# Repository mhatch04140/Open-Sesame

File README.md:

README
======
# Description
Open Sesame is a project to develope a prototype voice enabled car door opening Android application.

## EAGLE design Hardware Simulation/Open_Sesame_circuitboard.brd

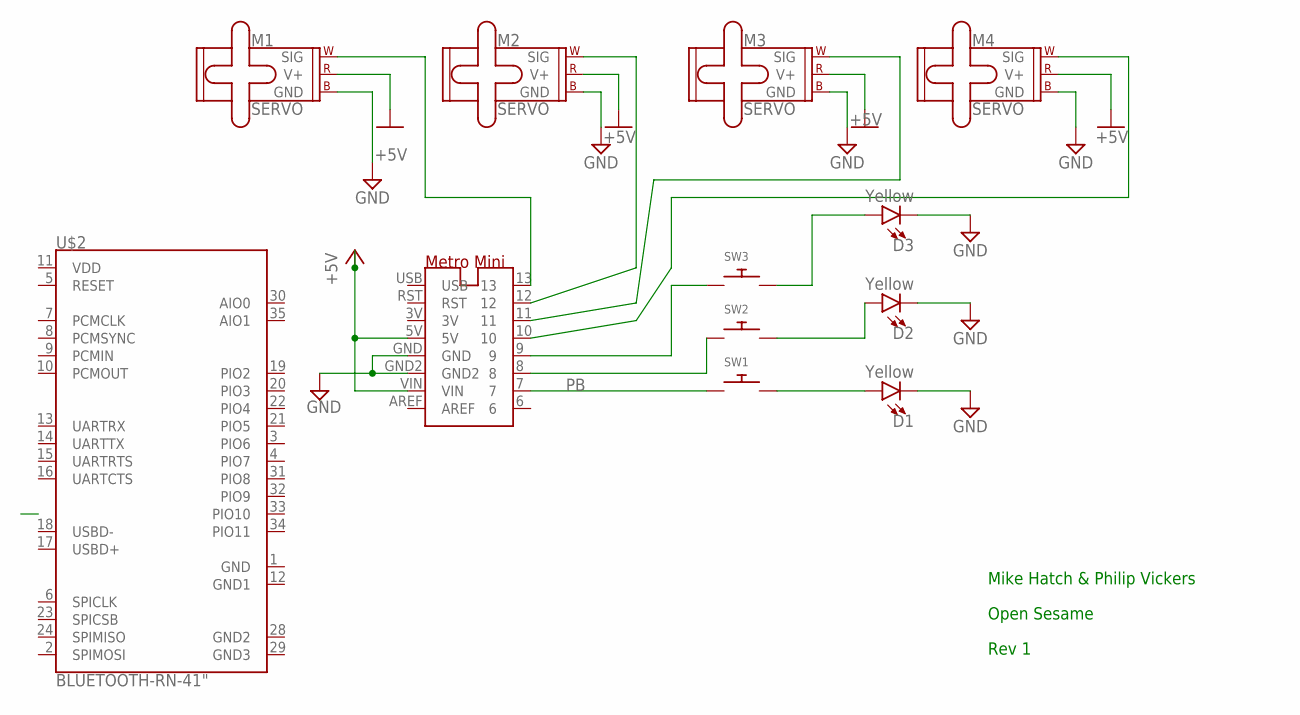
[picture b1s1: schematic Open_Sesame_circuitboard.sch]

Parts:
D1, D2, D3: Yellow; LED-0603
M1, M2, M3, M4: SERVO; 1X03
SW1, SW2, SW3: SWITCH_PUSHBUTTONC&K_KSS; BTN_CK_KSS
U$1: VTC_LIB_METROMINISHIELD; VTC_LIB_METROMINISHEILD
U$2: BLUETOOTH-RN-41"; RN41

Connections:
+5V: M1.2 (V+), M2.2 (V+), M3.2 (V+), M4.2 (V+), U$1.5V, U$1.VIN, U$2.11 (VDD)
GND: D1.C, D2.C, D3.C, M1.3 (GND), M2.3 (GND), M3.3 (GND), M4.3 (GND), U$1.GND, U$1.GND2, U$2.1 (GND)
unnamed: M1.1 (SIG), U$1.13
unnamed: M2.1 (SIG), U$1.12
unnamed: D1.A, SW1.P$2
unnamed: SW2.P$1, U$1.8
unnamed: D2.A, SW2.P$2
unnamed: SW3.P$1, U$1.9
unnamed: D3.A, SW3.P$2
unnamed: M3.1 (SIG), U$1.11
unnamed: M4.1 (SIG), U$1.10
unnamed: U$1.USB, U$2.17 (USBD+)
PB: SW1.P$1, U$1.7

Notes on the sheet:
Open Sesame
Mike Hatch & Philip Vickers
Rev 1

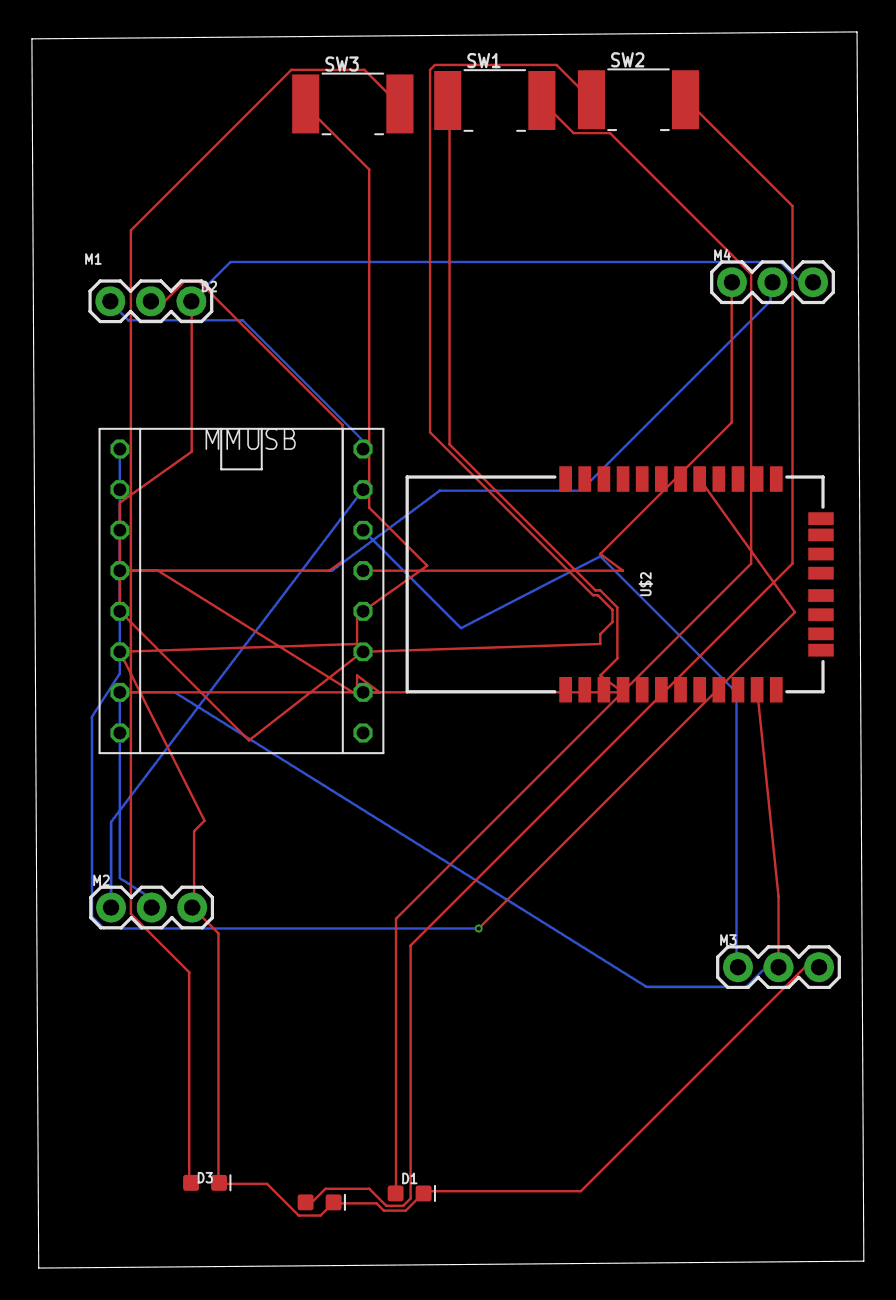
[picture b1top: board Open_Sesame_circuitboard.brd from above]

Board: 2 copper layers, 52.1 x 77.4 mm, 12 parts (0 on the bottom side), 13 nets.

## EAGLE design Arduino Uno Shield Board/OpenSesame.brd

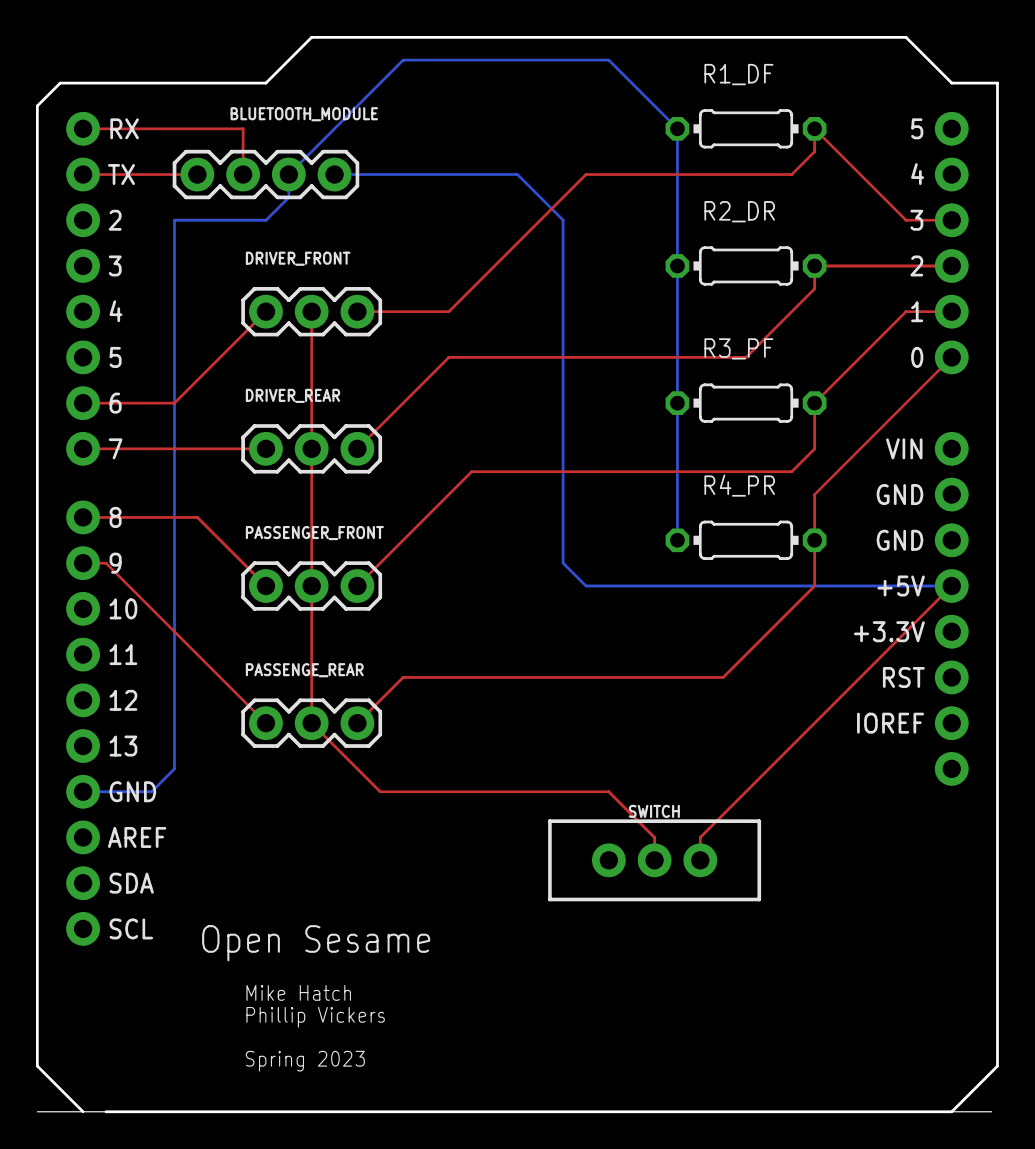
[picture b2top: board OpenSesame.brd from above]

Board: 2 copper layers, 53.3 x 59.7 mm, 11 parts (0 on the bottom side), 13 nets.

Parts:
B1: ARDUINO_UNO_R3_SHIELDBASIC; UNO_R3_SHIELD
BLUETOOTH_MODULE: 1X04
DRIVER_FRONT: 1X03
DRIVER_REAR: 1X03
PASSENGER_FRONT: 1X03
PASSENGE_REAR: 1X03
R1_DF, R2_DR, R3_PF, R4_PR: 0204/7
SWITCH: SWITCH_SPDT_PTH_11.6X4.0MM

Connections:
5V: B1.5V, BLUETOOTH_MODULE.1, SWITCH.1
5VOUT: DRIVER_FRONT.2, DRIVER_REAR.2, PASSENGER_FRONT.2, PASSENGE_REAR.2, SWITCH.2
A0: B1.A0, PASSENGE_REAR.3, R4_PR.2
A1: B1.A1, PASSENGER_FRONT.3, R3_PF.2
A2: B1.A2, DRIVER_REAR.3, R2_DR.2
A3: B1.A3, DRIVER_FRONT.3, R1_DF.2
D6: B1.D6, DRIVER_FRONT.1
D7: B1.D7, DRIVER_REAR.1
D8: B1.D8, PASSENGER_FRONT.1
D9: B1.D9, PASSENGE_REAR.1
GND1: B1.GND@2, BLUETOOTH_MODULE.2, R1_DF.1, R2_DR.1, R3_PF.1, R4_PR.1
RX: B1.RX, BLUETOOTH_MODULE.3
TX: B1.TX, BLUETOOTH_MODULE.4

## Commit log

2022-08-30 Added a placeholder README.
2022-09-13 organize documents
    organize documents
2022-09-13 organize folders
2022-09-13 Create requirements document
2022-09-13 moved read me
2022-09-13 moved requirements
2022-09-13 Create requirements
2022-09-13 Update requirements
2022-09-13 Introduction written for requirements
2022-09-14 edit intro
2022-09-18 Update requirements.md 9/17
2022-09-24 Update to requirements
2022-10-11 Added comments to the requirements document.
2022-10-11 Gantt Chart
2022-10-17 Update to pod file
2022-10-18 adjusted dates
2022-10-18 deleted one of the gantt chart folders
2022-10-18 Update to schematics
2022-10-18 Create Architecture and Design Document
2022-10-18 Create Link to Word Doc
2022-10-18 Update Link to Word Doc
2022-10-20 Reorganization of files
2022-10-20 Reorg. Cont.
2022-11-01 circuit board rough design
2022-11-01 Loaded drawings
2022-11-01 removed files
2022-11-01 Delete ~$rcuit Board_Schematic.docx
    no need for file
2022-11-03 worked on website
2022-11-03 update web code
2022-11-03 cleaning files
2022-11-08 added google doc
2022-11-10 first presentation
2022-11-14 Update presentation
2022-11-14 Update to Arduino code
    One servo working with bluetooth
2022-11-14 Updated presentation
2022-11-16 removed old docs
2022-12-06 Fixed ppt
2023-01-16 worked on mobile app
2023-01-17 app development and prototypimg
2023-01-22 updated Schedule
2023-01-22 changed name of file
2023-01-23 website work, added pages
2023-01-24 working on website manual page
2023-01-24 updated index and manual web page
2023-01-24 updated website pages
2023-01-28 website work
2023-01-28 added marketing slide
2023-01-30 Update to mobile application
2023-02-05 updated sch and webpages
2023-02-13 Mobile app update
2023-02-16 updated website
2023-03-01 Updated work
2023-03-06 Update to app, arduino, and schematics for shield
2023-03-07 Create Open Sesame Manual
2023-03-11 Update 3/11/23
2023-03-18 Weekly Update
2023-03-20 Cleaned up code. fixed a few things
2023-04-13 Update4/13
2023-04-20 updated the website
2023-04-20 final presentation
2023-04-23 Troubleshooting code
2023-04-23 presentation update
2023-04-28 Final Revisions

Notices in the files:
parts and their libraries:
SparkFun-Boards: Licensing: Creative Commons ShareAlike 4.0 International - https://creativecommons.org/licenses/by-sa/4.0
